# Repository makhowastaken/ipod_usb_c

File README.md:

# ipod_usb_c
USB C Breakout board for iPod devices

There is currently only one version. It is designed and tested for the 4th generation iPod (monochrome). This board will likely work in the 4th generation Photo as well but it's untested. Electrically, it is compatible with any iPod that uses USB. Fitting it in other models, however, may be a different story. 

BOM: 

* Port needed is [TYPE-C-31-M-12](https://lcsc.com/product-detail/USB-Type-C_Korean-Hroparts-Elec-TYPE-C-31-M-12_C165948.html). 
* [OSHpark link to order PCBs](https://oshpark.com/shared_projects/0PFqSP8G) or you can upload the zip file in the gerbers directory to your preferred fab. 0.8mm thickness highly recommended.
* some short, thin wire (four strips about an inch or 25 mm long)
* 2x 5.1k 0603 resistors
* A small spacer -- I used a bit of broken plastic I had on my desk. This just makes it so the board sits flat over the click wheel FFC
* One longer PCB screw because the original screw is too short to go through the new board, spacer, and original board. I used a long GBA SP screw. 

The resistors are optional as long as you do not require USB C host compatibility. 

Here is how it can be wired on a 4th gen monochrome iPod

For the actual install, you will need a drill, some drill bits (final diameter 1/8th inch or approximately 3mm) and some needle files. This REQUIRES cutting a hole in the metal back of your iPod. Use calipers to measure what you need to cut for the opening. 

Otherwise you can see my video here: https://youtu.be/GwSPD8ESmN4

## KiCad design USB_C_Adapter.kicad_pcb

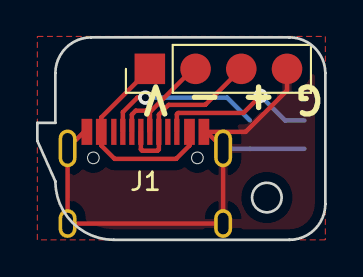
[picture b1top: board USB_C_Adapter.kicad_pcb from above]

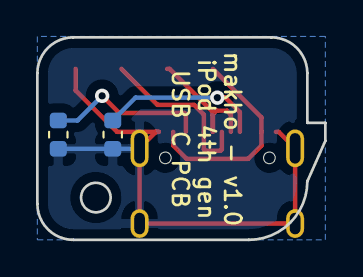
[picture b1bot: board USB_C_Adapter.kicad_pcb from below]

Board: 2 copper layers, 16.0 x 11.2 mm, 4 parts (2 on the bottom side), 6 nets.

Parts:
J1: USB_C_Receptacle_USB2.0; TYPE-C-31-M-12
J2: Conn_01x04_Female; PinHeader_1x04_P2.54mm_Vertical
R1, R2: 5.1k; R_0603_1608Metric

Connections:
GND: J1.A1|B12, J1.B1|A12, J1.GND, J2.4, R1.2, R2.2
unnamed: J1.A4|B9, J1.B4|A9, J2.1
unnamed: J1.A5, R1.1
unnamed: J1.A6, J1.B6, J2.3
unnamed: J1.A7, J1.B7, J2.2
unnamed: J1.B5, R2.1

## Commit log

2020-06-28 Add files via upload
    added PCB files
2020-06-28 Add files via upload
    added renders
2020-06-28 Add files via upload
    added more images for the readme
